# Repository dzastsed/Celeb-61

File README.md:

# Celeb-61 
*a nod towards Celeb-17 nickname of Makise Kurisu*

Working beta version with 2025-05 board design. No more bodges!
# DISCLAIMER
This design is still a prototype, stuff may break and/or change. You've been warned.

## New features:

* usb-c to ttl adapter (optional)

* usb-c power supply (optional)

* better layout

* mounting screw holes

Preview pics 

Bottom

Top

Top, artwork edition (legacy design in `old project and gerbers (do not use)` folder)

# Schematic

# Firmware

Regular clock, and clock with scrambling code implemented are included `firmware` folder.

- Regular firmware:
Just does the clock function, and nothing more. It probably isn't even up to date with current board design. Not recommended to use.

- Scramlin' firmware:
Does character scramble every hour (after 30 seconds pass at 31 minute mark) to prevent cathode poisoning. Up to date. Use this firmware.

# Known issues

None so far?

# Setup guide

refer to [installation.md](https://github.com/dzastsed/Celeb-61/blob/main/installation.md)

# Parts list

refer to [parts.md](https://github.com/dzastsed/Celeb-61/blob/main/parts.md)

# Future improvements

ESP32 support - for wi-fi clock sync etc.

Diode on TTL module power rail to prevent powering it from secondary USB port (or complete removal of 2ndary USB port as this board can be powered by TTL module just fine).

Different board versions for different tube footprints.

A physical switch of some sort to turn the clock off while it's still plugged in

More covering for high voltage parts

# Credits

TheMobas0 - for help on making the scramble code

Greatsccott! - original board design

Elli - for drawing Makise Kurisu art

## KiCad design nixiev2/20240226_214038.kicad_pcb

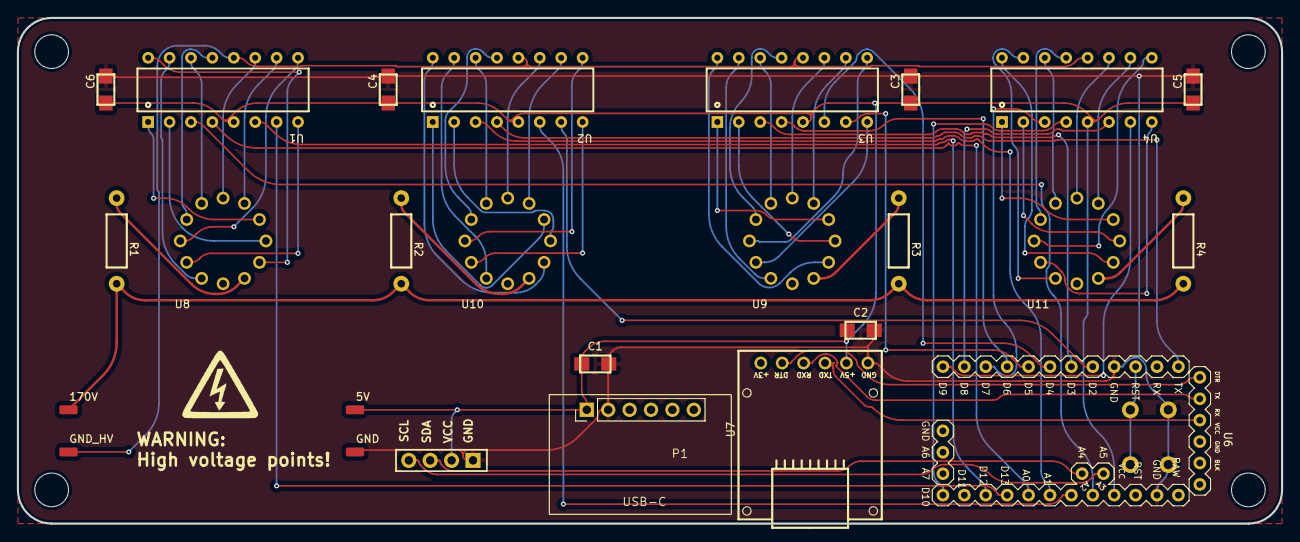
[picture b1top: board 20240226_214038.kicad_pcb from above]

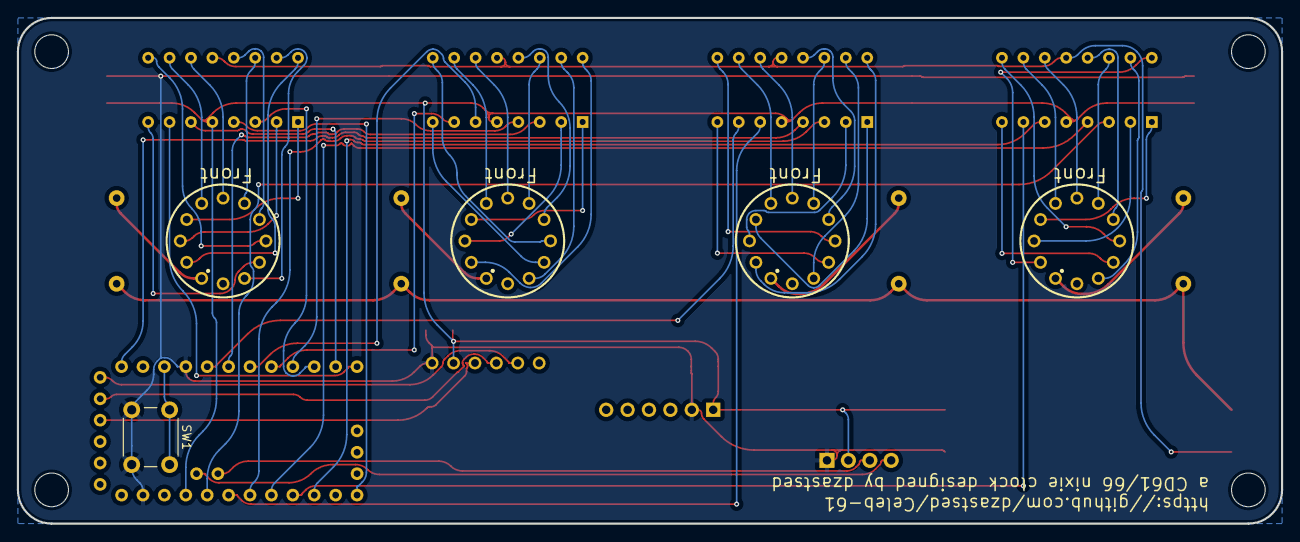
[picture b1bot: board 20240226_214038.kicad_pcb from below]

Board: 2 copper layers, 150.0 x 60.0 mm, 27 parts (5 on the bottom side), 70 nets.

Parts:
5V: 5V; SOLDERPAD
170V: 170V; SOLDERPAD
C1, C2: 10uF; CAPACITOR-SMD-1206
C3, C4, C5, C6: 100nF; CAPACITOR-SMD-1206
CLK1: ZS_042/DS3231; ZS-042-DS3231
GND: GND; SOLDERPAD
GND_HV: GND_HV; SOLDERPAD
P1: USB_C_Plug_USB2.0; USBC breakout
R1, R2, R3, R4: 20k; AXIAL-0.4
SW1: SW_Push; SW_PUSH_6mm
U1, U2, U3, U4: K155ID1/SN74141; DIP16
U6: ARDUINO PRO-MINI COPY; ARDUINOPROMINI_ARDUINO_PRO_MINI
U7: USB_TO_TTL_CH340E
U8, U9, U10, U11: Nixie_Tube_CD66_Tomas5054; NEC_NIXIE_TUBE_CD66A_TOMAS5054

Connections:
170v: 170V.1, R1.2, R2.2, R3.2, R4.2
+5V: 5V.1, C1.1, C2.1, C3.2, C4.2, C5.2, C6.2, CLK1.3 (VCC), P1.1 (VBUS), U1.5 (VCC), U2.5 (VCC), U3.5 (VCC), U4.5 (VCC), U6.VCC, U7.5 (+5V)
A1: U3.3 (A), U6.D3
A2: U4.3 (A), U6.D7
A3: U1.3 (A), U6.A3
A4: U2.3 (A), U6.A1
B1: U3.6 (B), U6.D4
B2: U4.6 (B), U6.D8
B3: U1.6 (B), U6.D12
B4: U2.6 (B), U6.A2
C1: U3.7 (C), U6.D5
C2: U4.7 (C), U6.D9
C3: U1.7 (C), U6.D13
C4: U2.7 (C), U6.D2
D1: U3.4 (D), U6.D6
D2: U4.4 (D), U6.D10
D3: U1.4 (D), U6.A0
D4: U2.4 (D), U6.TX
GND: C1.2, C2.2, C3.1, C4.1, C5.1, C6.1, CLK1.4 (GND), GND.1, P1.2 (GND), SW1.2, U6.GND, U6.GND@1 (GND), U7.6 (GND)
GND_HV: GND_HV.1, U1.12 (GND), U2.12 (GND), U3.12 (GND), U4.12 (GND)
unnamed: R1.1, U8.A
unnamed: R2.1, U10.A
unnamed: R3.1, U9.A
unnamed: R4.1, U11.A
unnamed: SW1.1, U6.RST@1 (RST)
unnamed: U6.RX@1 (RXI), U7.4 (TXD)
unnamed: U6.TX@1 (TX0), U7.3 (RXD)
unnamed: U6.DTR, U7.2 (DTR)
SCL: CLK1.1 (SCL), U6.A5
SDA: CLK1.2 (SDA), U6.A4
U8-0: U1.16 (0), U8.(.) (K(.))
U8-1: U1.15 (1), U8.1 (K(1))
U8-2: U1.8 (2), U8.2 (K(2))
U8-3: U1.9 (3), U8.3 (K(3))
U8-4: U1.13 (4), U8.4 (K(4))
U8-5: U1.14 (5), U8.5 (K(5))
U8-6: U1.11 (6), U8.6 (K(6))
U8-7: U1.10 (7), U8.7 (K(7))
U8-8: U1.1 (8), U8.8 (K(8))
U8-9: U1.2 (9), U8.9 (K(9))
U9-0: U3.16 (0), U9.(.) (K(.))
U9-1: U3.15 (1), U9.1 (K(1))
U9-2: U3.8 (2), U9.2 (K(2))
U9-3: U3.9 (3), U9.3 (K(3))
U9-4: U3.13 (4), U9.4 (K(4))
U9-5: U3.14 (5), U9.5 (K(5))
U9-6: U3.11 (6), U9.6 (K(6))
U9-7: U3.10 (7), U9.7 (K(7))
U9-8: U3.1 (8), U9.8 (K(8))
U9-9: U3.2 (9), U9.9 (K(9))
U10-0: U2.16 (0), U10.(.) (K(.))
U10-1: U2.15 (1), U10.1 (K(1))
U10-2: U2.8 (2), U10.2 (K(2))
U10-3: U2.9 (3), U10.3 (K(3))
U10-4: U2.13 (4), U10.4 (K(4))
U10-5: U2.14 (5), U10.5 (K(5))
U10-6: U2.11 (6), U10.6 (K(6))
U10-7: U2.10 (7), U10.7 (K(7))
U10-8: U2.1 (8), U10.8 (K(8))
U10-9: U2.2 (9), U10.9 (K(9))
U11-0: U4.16 (0), U11.(.) (K(.))
U11-1: U4.15 (1), U11.1 (K(1))
U11-2: U4.8 (2), U11.2 (K(2))
U11-3: U4.9 (3), U11.3 (K(3))
U11-4: U4.13 (4), U11.4 (K(4))
U11-5: U4.14 (5), U11.5 (K(5))
U11-6: U4.11 (6), U11.6 (K(6))
U11-7: U4.10 (7), U11.7 (K(7))
U11-8: U4.1 (8), U11.8 (K(8))
U11-9: U4.2 (9), U11.9 (K(9))

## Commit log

2024-05-01 project and gerber file
2024-05-01 gerber with artwork
2024-12-06 matching firmware
2024-12-06 late 2024 updates
2024-12-06 late 2024 update
2025-05-18 latest project as of this moment
2025-07-14 Delete nixiev2 directory
    rework of repo
2025-07-14 latest project
2025-07-14 rework
2026-03-21 DST autochange addon
2026-06-10 update for future ideas
